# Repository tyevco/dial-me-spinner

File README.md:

# dial-me-spinner

**Docs site:** <https://tyevco.github.io/dial-me-spinner/>

A Bluetooth dial spinner about 70 mm across, built on the nRF52840. A heavy,
balanced stainless flywheel ring spins around a stationary centre that holds a
colour OLED and a ring of 48 addressable RGB LEDs. You can press the whole top
to click. A tiny actuator switches the ring electronically between **free
spin** and **magnetic click detents**, and it holds either position with zero
power.

The same hardware serves three uses:

* **Game / decision spinner.** You flick the ring and a prize wheel animates on
  the LEDs and the OLED, with a tick on every detent and the result shown when
  it stops.
* **PC / phone controller.** It works like a Surface Dial: a BLE or USB HID
  Radial Controller on Windows, and a wheel or consumer-control device on
  macOS, Linux, Android and iOS.
* **Fidget toy.** Long free spins or clicky spins, with a spin and RPM counter.

> **Status: rev A. Schematics and both PCBs are generated and routed, and the
> fab outputs are written; nothing has been built or tested.** The schematics
> of both boards pass ERC. The only report is one intended pin pair that
> `build.py` waives and lists (U21's QOD tied to its VOUT). Both boards are
> placed and routed by `layout.py` (Freerouting first, then the grid router
> `finish_route.py` for the connections it leaves open) and pass KiCad DRC with
> schematic parity: 0 errors and 0 unconnected on both, no warnings on the main
> board, two silk-to-edge warnings on the base board. `release.py` wrote the
> fab outputs into `hardware/fab/main/` and `hardware/fab/base/` only after
> that gate passed. The mechanical model's clash check of the routed boards
> reports only the intended contacts. A SPICE suite (`hardware/sim/`, [docs/simulation.md](docs/simulation.md))
> checks the analog design against the netlists; the part changes it drove
> are in the schematics. No prototype has been built and no firmware has been written.
> Every runtime, force and spin-time figure in the docs is a calculation or
> simulation that still has to be verified on a prototype.

## Features (rev A design)

| | |
|---|---|
| Size | Ø70 × 36 mm. Stationary centre, spinning 316L stainless ring (≈ 117 g, OD 70 / ID 54 / 10 mm) on a single 608 bearing |
| Detents | 24 clicks per turn, strength continuously variable from 0 to about 16.5 mN·m, or free spin (the detent magnet's residual cogging is 2.7 µN·m; the stepper's own cogging still has to be bench-tested, [mechanical §7](docs/mechanical.md#7-detent-mechanism)). Switched by a micro linear stepper with a self-locking lead screw (zero holding power) |
| Rotation sensing | TI TMAG5273 3D Hall sensor reading the same 48-magnet track. Interpolated angle, about 0.05–0.1° after self-calibration, plus µA-level wake on rotation |
| Display | 1.5 in 128×128 RGB PMOLED (SSD1351) behind a Ø30 mm round window |
| Lights | 48 × WS2812C-2020-V6 RGB LEDs under an opal diffuser ring, 2 per detent |
| Input | Press-down click (the whole top floats on springs over a centre switch), rotation, tap and pick-up (LIS2DW12 accelerometer) |
| Sound | Magnet-free piezo for detent ticks and UI beeps |
| Radio | nRF52840 module (Raytac MDBT50Q-U1MV2, u.FL) with an off-board flex antenna in the base. BLE HID, a custom GATT service for a companion app, and USB HID |
| NFC | NFC-A tag emulation (Type 2 / Type 4) on the nRF52840 NFCT, with a coil in the top cover. Phones read it; the spinner cannot read tags (the phone app reads one and sends the content over BLE) |
| Power | 1S LiPo of about 1000 mAh, TI BQ25180 power-path charger, USB-C. Ship mode, about 38 µA sleep (25 °C typical; [power budget](docs/architecture.md#8-power-budget-and-battery-life)) |
| Estimated runtime | About 9 h of continuous game mode, about 4 weeks of typical desk-controller use per charge (see the [power budget](docs/architecture.md#8-power-budget-and-battery-life)) |

## Documentation

| Document | Contents |
|---|---|
| [docs/architecture.md](docs/architecture.md) | System overview, how each requirement is met, block diagram, board partition and link, subsystem decisions with the alternatives that were rejected, power tree, power budget and battery life, RF strategy, risk register, open decisions, rough BOM cost |
| [docs/assembly.md](docs/assembly.md) | Fabrication and assembly: JLCPCB order settings, sourcing, the link harness and antenna coax, magnet track, bearing prep, rotor balancing, mechanical assembly order |
| [docs/bringup.md](docs/bringup.md) | Bring-up and acceptance tests (steps B-x), from bare PCBA to an accepted unit |
| [docs/mechanical.md](docs/mechanical.md) | Mechanical design: stack-up and where SPEC §8 is not buildable as written, bearing, flywheel and balancing, magnet track, detent mechanism, press click, antenna placement, drop, feet, assembly order, mechanical BOM, calculations |
| [docs/firmware.md](docs/firmware.md) | Firmware architecture plan (nRF Connect SDK / Zephyr, MCUboot), including the BQ25180 register init table (§13.1). A plan only: no firmware code exists yet |
| [docs/simulation.md](docs/simulation.md) | The SPICE suite in `hardware/sim/`: how to run it, how a test is built, what each block covers; the latest values are on its [results page](hardware/sim/results/report.md) |
| [docs/display-study.md](docs/display-study.md) | Rev-B study (future work): a larger round touch AMOLED. Rev A keeps the SSD1351 OLED |
| [hardware/design/SPEC.md](hardware/design/SPEC.md) | **Architecture of record** for the schematics: boards, link pinout, power tree, nRF52840 pin map, per-sheet contents, mechanical stack-up |
| [hardware/tools/README.md](hardware/tools/README.md) | The Python → KiCad generator toolchain |

## Repository layout

```
docs/                    design documentation (start with architecture.md;
                         simulation.md for the SPICE suite, display-study.md
                         for rev B)
hardware/
  design/                the circuit as code
    SPEC.md              architecture of record (what the schematics implement)
    nets.py              pin map and the shared net names (the "capture contract")
    build.py             generates the schematics (.kicad_sch), project file and
                         netlist from the sheet modules, and runs ERC
    layout.py            generates the boards (.kicad_pcb) from the netlists:
                         SPEC §8 placement of the constrained parts, clustering
                         of the rest, outline, keep-outs, zones, fiducials,
                         optional Freerouting autoroute, then the grid router
                         (hardware/tools/finish_route.py) for what it leaves
                         open, clean-up (GND stitching vias, silkscreen
                         references), then DRC
    release.py           fab and review outputs into hardware/fab/<board>/:
                         gerbers, JLCPCB BOM + CPL, ORDER-NOTES.md, schematic and
                         board PDFs, 3D renders; refuses to write them unless DRC
                         and schematic parity are clean
    jlc_offsets.json     cached per-LCSC-part rotation/origin corrections for the
                         JLC CPL (written by tools/jlc_cpl.py)
    sheets/              one Python module per schematic sheet
                         main board: main_power, mcu, display, leds, sensors, detent
                         base board: base
  tools/                 generator toolchain: S-expression I/O, symbol/footprint
                         generation, schematic writer, PCB builder, placer, fab outputs
    finish_route.py      grid router that completes the connections Freerouting
                         leaves open (A* on F.Cu / In2.Cu / B.Cu with through
                         vias, rip-up of unlocked signal copper); KiCad DRC
                         re-checks every connection it adds
    silk.py              places silkscreen references clear of pads, other silk
                         and the board edge
    jlc_cpl.py           fits JLC's EasyEDA footprints to the KiCad ones and writes
                         the CPL (top θ+α, bottom 180−θ+α); simulates JLC's
                         placement of every row and stops on a pad off copper
    tests/               CPL check tests (pytest; needs pcbnew)
  kicad/                 generated KiCad 10 projects (main/, base/): schematics from
                         build.py, .kicad_pcb from layout.py
  fab/                   generated by release.py, one directory per board (main/,
                         base/): gerbers.zip, *-BOM-JLCPCB.csv, *-CPL-JLCPCB.csv,
                         ORDER-NOTES.md (DNP list, bottom-side parts, board-only
                         parts), drc-parity.rpt (the DRC + schematic-parity
                         gate's report), PDFs, renders
  mechanical/            enclosure and rotor CAD (OpenSCAD), calculations, renders
                         and STLs; board parts imported from the generated PCBs
                         (extract_board_parts.py) for the clash check
  sim/                   SPICE test suite (ngspice + pytest) that builds its
                         decks from the generated netlists: tests/test_*.py,
                         IC models in models/, report written to results/
                         when run (docs/simulation.md)
firmware/                (planned) nRF Connect SDK / Zephyr application
```

The schematics in `hardware/kicad/` are **generated**. Do not hand-edit the
`.kicad_sch` files. Change the sheet modules in `hardware/design/sheets/` (and
SPEC.md or nets.py if the architecture changes), then rebuild.

## Regenerating the KiCad projects

Requirements:

* **KiCad 10** (10.0.8), providing:
  * `kicad-cli`;
  * the `pcbnew` Python module, used to write custom footprints and by
    `layout.py` and `release.py`;
  * the stock libraries and project template in `/usr/share/kicad`.
    `KICAD10_SYMBOL_DIR` overrides the symbol path (used by `build.py`).
    `KICAD10_FOOTPRINT_DIR` overrides the footprint path, and only `layout.py`
    reads it. The project template path
    (`/usr/share/kicad/template/kicad.kicad_pro`) is fixed in `schgen.py`.
* **Python 3.10+**, with numpy for `layout.py`, and matplotlib for the grid router.
* **poppler-utils** (`pdftoppm`), only for `--render`.
* Optionally `xvfb-run`, which `release.py` uses for headless 3D renders.
* For autorouting only: **Java 21** and the **Freerouting 2.1.x** jar, given
  by `FREEROUTING_JAR`.

From the repository root:

```sh
# Both boards: writes hardware/kicad/main/ and hardware/kicad/base/,
# runs ERC and exports a netlist for each
python3 hardware/design/build.py

# One board, plus a PDF and one PNG per sheet for review
python3 hardware/design/build.py --board main --render

# Scratch build of selected sheets into another directory, without ERC
python3 hardware/design/build.py --board main --only leds sensors --out /tmp/scratch --no-erc
```

Each board directory receives:
* `dial-me-spinner-<board>.kicad_pro`, the `.kicad_sch` sheets and a `.net`
  netlist;
* the ERC report `erc.rpt`;
* a project-local library in `lib/` (`dial_spinner.kicad_sym` and
  `dial_spinner.pretty`).

Open the `.kicad_pro` in KiCad 10 to inspect the result. `build.py` exits
non-zero if its own connectivity checks fail.

Boards and fab outputs (after `build.py`, which writes the netlists they read):

```sh
# Place both boards and run DRC; add --route to autoroute with Freerouting
# (--minutes N is the Freerouting time budget of the first attempt, default 30,
# and attempt k gets k x N; --attempts N, default 3, re-runs it while
# connections remain; whatever is still open then goes to the grid router;
# --resume continues routing the board as it is; --complete runs only the grid
# router on it; --finish only cleans up an already routed board)
python3 hardware/design/layout.py [--board main|base] [--route] [--minutes N] [--attempts N] [--resume] [--complete] [--finish]

# Gerbers, JLCPCB BOM + CPL, ORDER-NOTES.md, PDFs and 3D renders into
# hardware/fab/<board>/; stops if DRC or schematic parity reports an error
# (--force writes a review-only package)
python3 hardware/design/release.py [--board main|base] [--force]
```

The CPL corrections come from `hardware/design/jlc_offsets.json`, so
`release.py` needs no network access. It stops if a placed part has no entry
there; `jlc_cpl.update_offsets()` adds one by fetching that part's EasyEDA
footprint, and caches its pads. Before writing the CPL, `release.py` puts
those EasyEDA pads down at each row's point and angle, the way JLC places the
part, and stops if any pad lands off copper or on a differently numbered pad
of the same name (a symmetric package turned 180° still lands on copper, so
the numbers are the only sign). `python3 -m pytest hardware/tools/tests -q`
checks that this check passes on both boards and catches a wrong rotation or
origin. The EasyEDA footprint titles and pad centres in `jlc_offsets.json` come
from the JLCEDA/EasyEDA Official Library ([lceda.cn](https://lceda.cn/),
[easyeda.com](https://easyeda.com)), whose copyright belongs to JLCEDA/EasyEDA.

## Running the SPICE suite

The suite reads the netlists that `build.py` writes, so run it after a
schematic change. It needs ngspice 42 or newer and pytest, numpy and scipy
([docs/simulation.md](docs/simulation.md)):

```sh
python3 -m pytest hardware/sim -q                  # everything
python3 -m pytest hardware/sim -q -m "not slow"    # skip the long Monte Carlo sweeps
```

It writes `hardware/sim/results/report.md` and `results.json`. A check that
shows a real design problem is a strict `xfail` with the reason, so it cannot
quietly start passing.

## Status and next steps

* **Done:** subsystem research with independent verification. Architecture
  (SPEC.md). Generator toolchain. Schematics of both boards, ERC-clean
  apart from the one documented `build.py` waiver.
  Both boards placed and routed (`layout.py`: SPEC §8 placement of the
  constrained parts, clustering of the rest, Freerouting, then the grid router
  `finish_route.py`), DRC clean with schematic parity.
  The fab-output script `release.py`, which writes Gerbers, the JLCPCB BOM and
  CPL (rotations corrected per LCSC part), ORDER-NOTES.md, PDFs and renders
  behind a DRC and schematic-parity gate, and its outputs for both boards in
  `hardware/fab/`. The placement fixes from the
  mechanical model's clash check (module u.FL facing outward, link connector
  J1 at r 19.5, the 2.95 mm SM04B battery connector, R42 clear of the cover
  skirt), after which the check reports only the intended contacts. The SPICE
  suite in `hardware/sim/` and the part changes it drove (VBUS series resistor
  R12, a second USB ESD array U12 at the module, the OLED load switch's QOD
  tied to its output, R4 68 Ω for the LED rail discharge, 25 V VSYS caps, base
  C1 and R4). Assembly, bring-up, mechanical, simulation and firmware-plan
  documents.
* **In progress:** the SPEC items in mechanical §3A. The remaining strict
  `xfail`s of the SPICE suite are firmware-dependent rules (written into
  firmware.md and SPEC §5) or accepted rev-A risks, such as the USB ESD
  margin with a short harness, the actuator thrust and the OLED boost's
  FB-bias spread ([docs/simulation.md](docs/simulation.md)).
* **Not done:** no prototype has been built or tested, and no firmware code has
  been written. Every item marked "to verify on prototype" in the docs is
  still open. The detent actuator's thrust margin is open (architecture risk
  R4).
* **Next:**
  * close the pre-order checks in [assembly §2.4](docs/assembly.md#24-pre-order-checks-do-them-in-the-gerber-viewer-not-only-in-kicad)
    and [§13](docs/assembly.md#13-open-items-and-tvp-list-assembly)
    (LED-cavity silk, boost-inductor spacing), then order both boards with
    the outputs in `hardware/fab/main/` and `hardware/fab/base/`: two-sided assembly
    for the main board, top side only for the base board (4-layer, ENIG), the
    MDBT50Q through JLC Global Sourcing or consignment, the DNP list from
    ORDER-NOTES.md;
  * a printed mechanical mock-up to check the antenna shelf, the harness and
    coax path and the ring's ESD bleed path, and to measure the RF antenna
    (VNA/RSSI), spin-down and detent feel, plus a bench test of the stepper's
    free-mode cogging before the PCB order;
  * bring-up of the first prototype ([docs/bringup.md](docs/bringup.md)) and
    the items to verify on it;
  * firmware, following [docs/firmware.md](docs/firmware.md).
* Known issues and open decisions are tracked in
  [architecture §10–§13](docs/architecture.md#10-risk-register) and
  [assembly §13](docs/assembly.md#13-open-items-and-tvp-list-assembly).

Long-lead parts to order early: the SSD1351 OLED panel (0 stock at major
distributors in Oct 2026), the MDBT50Q-U1MV2 module (0 stock at JLC: use JLC
Global Sourcing or consign it) and the Molex 146153-0100 antenna (DigiKey/Mouser;
LCSC stocks only the -0050, which is too short).

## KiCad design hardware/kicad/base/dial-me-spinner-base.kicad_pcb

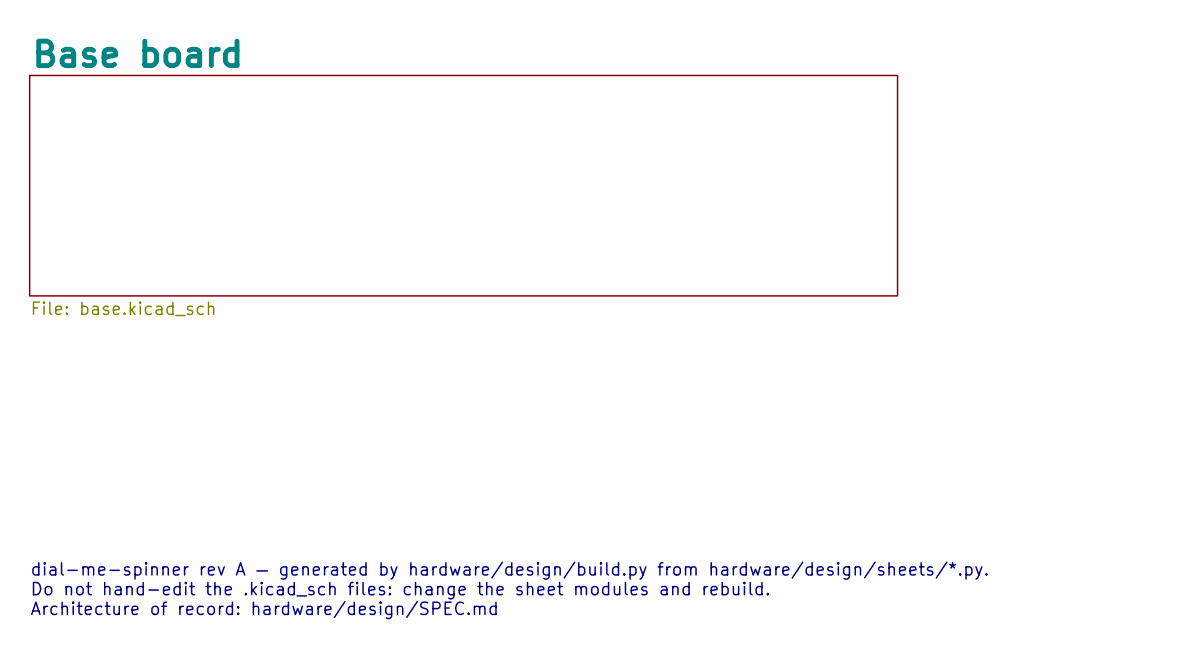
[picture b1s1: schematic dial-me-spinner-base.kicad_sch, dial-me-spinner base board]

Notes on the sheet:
dial-me-spinner rev A — generated by hardware/design/build.py from hardware/design/sheets/*.py. Do not hand-edit the .kicad_sch files: change the sheet modules and rebuild. Architecture of record: hardware/design/SPEC.md

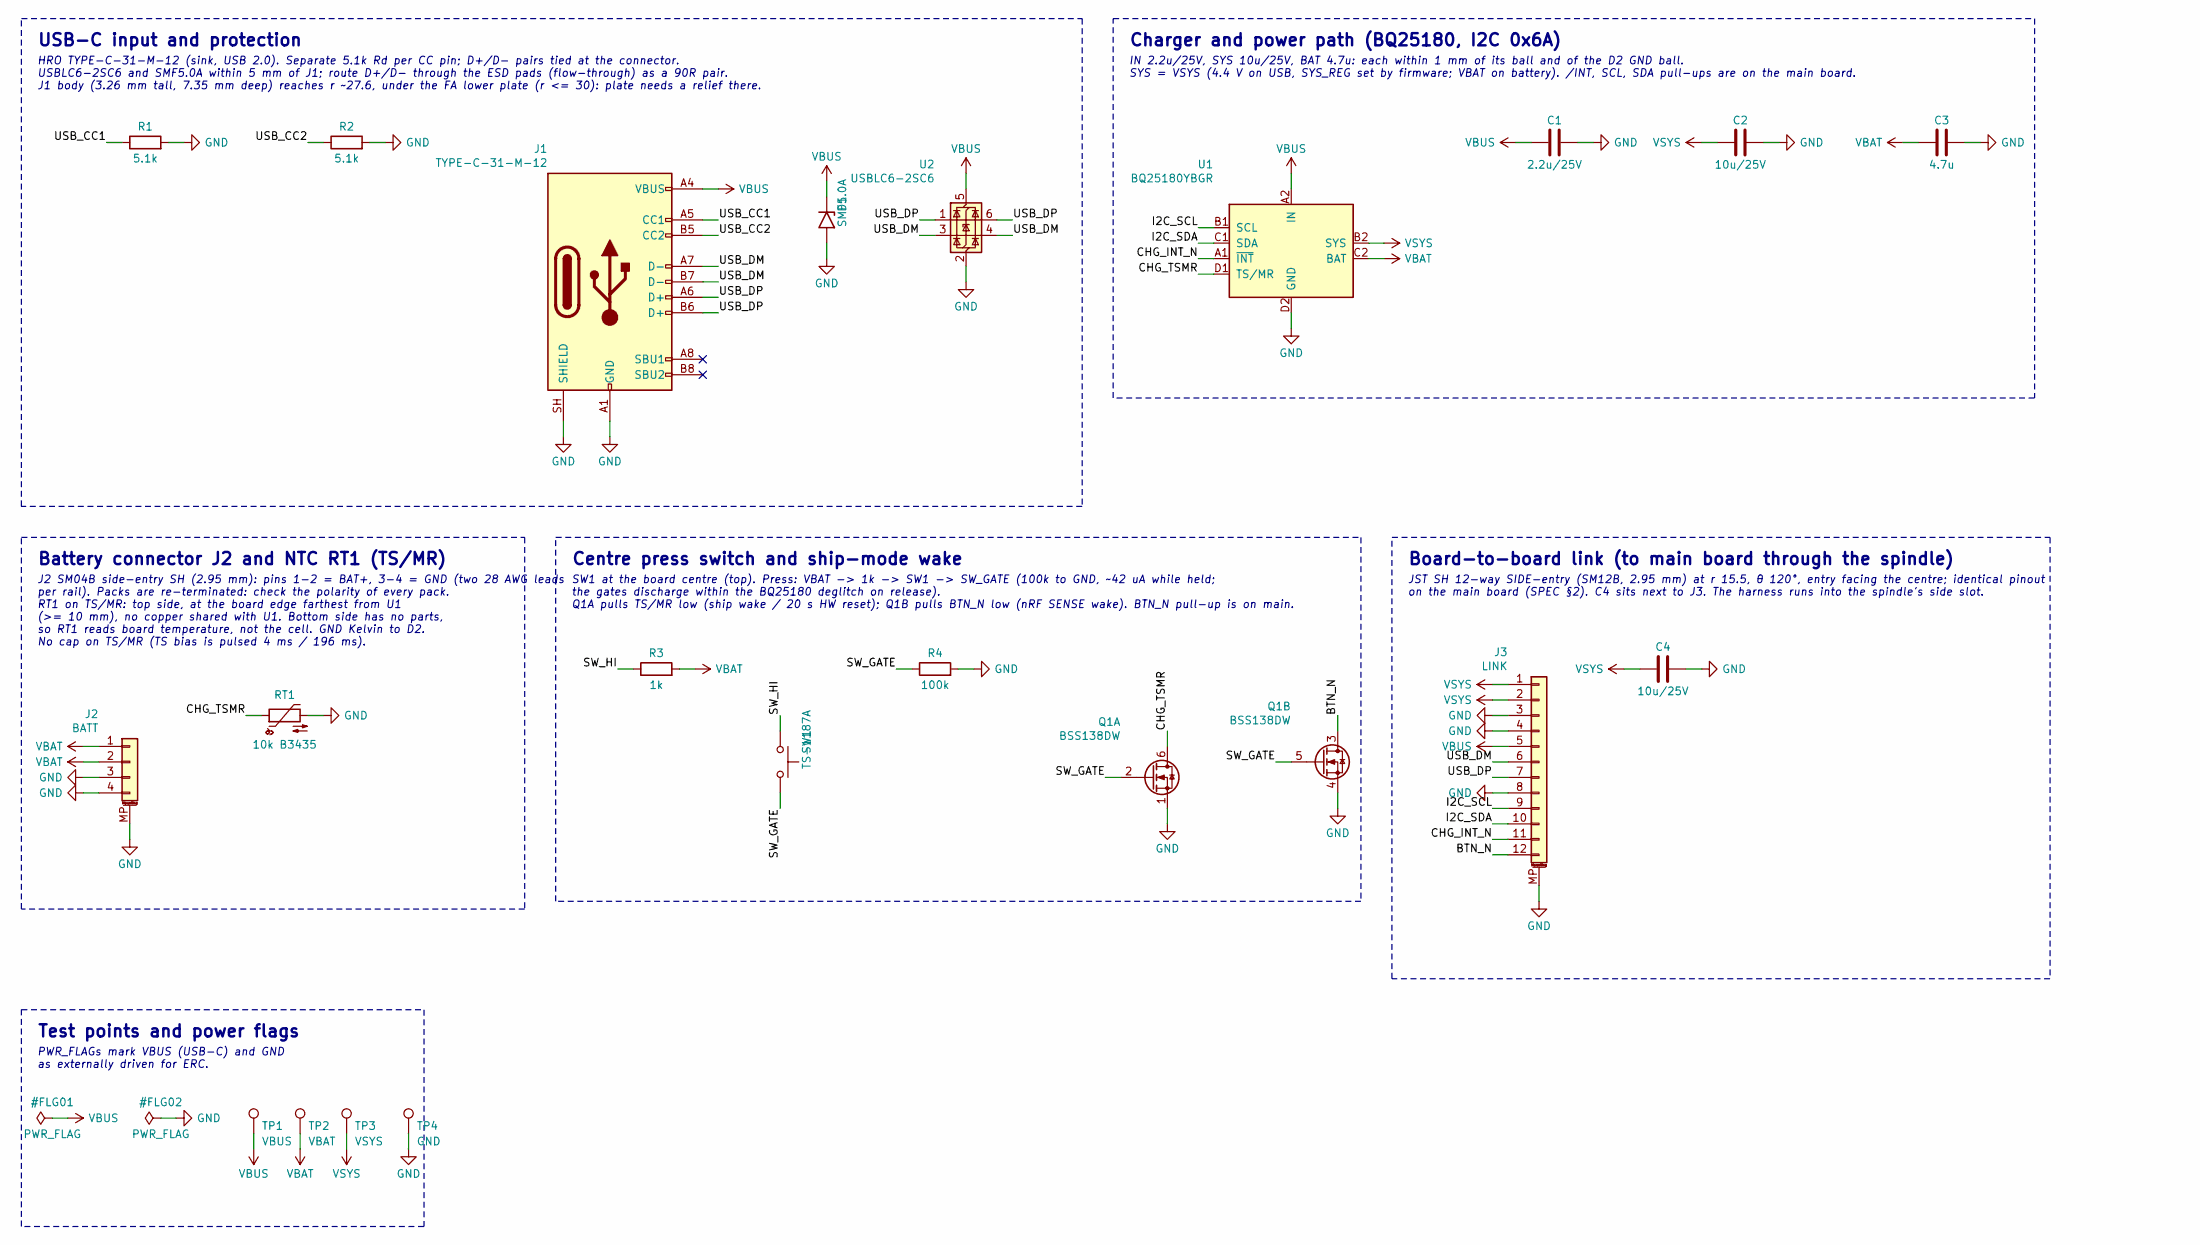
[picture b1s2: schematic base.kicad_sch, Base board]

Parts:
C1: 2.2u/25V; C_0805_2012Metric; MPN CC0805KKX7R8BB225; LCSC C277470
C2, C4: 10u/25V; C_0603_1608Metric; MPN CL10A106MA8NRNC; LCSC C96446
C3: 4.7u; C_0603_1608Metric; MPN CL10A475KO8NNNC; LCSC C19666
D1: SMF5.0A; D_SMF; MPN SMF5.0A; LCSC C151296
J1: TYPE-C-31-M-12; USB_C_Receptacle_HRO_TYPE-C-31-M-12; MPN TYPE-C-31-M-12; LCSC C165948
J2: BATT; JST_SH_SM04B-SRSS-TB_1x04-1MP_P1.00mm_Horizontal; MPN SM04B-SRSS-TB(LF)(SN); LCSC C160404
J3: LINK; JST_SH_SM12B-SRSS-TB_1x12-1MP_P1.00mm_Horizontal; MPN SM12B-SRSS-TB(LF)(SN); LCSC C160411
Q1: BSS138DW; SOT-363_SC-70-6; MPN BSS138DW-7-F; LCSC C154900
R1, R2: 5.1k; R_0402_1005Metric; MPN 0402WGF5101TCE; LCSC C25905
R3: 1k; R_0402_1005Metric; MPN 0402WGF1001TCE; LCSC C11702
R4: 100k; R_0402_1005Metric; MPN 0402WGF1003TCE; LCSC C25741
RT1: 10k B3435; R_0402_1005Metric; MPN NCP15XH103F03RC; LCSC C77131
SW1: TS-1187A; SW_Push_1P1T_XKB_TS-1187A; MPN TS-1187A-B-A-B; LCSC C318884
TP1: VBUS; TestPoint_Pad_D1.0mm
TP2: VBAT; TestPoint_Pad_D1.0mm
TP3: VSYS; TestPoint_Pad_D1.0mm
TP4: GND; TestPoint_Pad_D1.0mm
U1: BQ25180YBGR; Texas_DSBGA-8_1.04x1.59mm_Layout2x4_P0.4mm_YBG0008; MPN BQ25180YBGR; LCSC C3682423
U2: USBLC6-2SC6; SOT-23-6; MPN USBLC6-2SC6; LCSC C7519

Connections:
/Base board/BTN_N: J3.12, Q1.3 (D)
/Base board/CHG_INT_N: J3.11, U1.A1 (~INT)
/Base board/CHG_TSMR: Q1.6 (D), RT1.1, U1.D1 (TS/MR)
/Base board/I2C_SCL: J3.9, U1.B1 (SCL)
/Base board/I2C_SDA: J3.10, U1.C1 (SDA)
/Base board/SW_GATE: Q1.2 (G), Q1.5 (G), R4.1, SW1.2
/Base board/SW_HI: R3.1, SW1.1
/Base board/USB_CC1: J1.A5 (CC1), R1.1
/Base board/USB_CC2: J1.B5 (CC2), R2.1
/Base board/USB_DM: J1.A7 (D-), J1.B7 (D-), J3.6, U2.3 (I/O2), U2.4 (I/O2)
/Base board/USB_DP: J1.A6 (D+), J1.B6 (D+), J3.7, U2.1 (I/O1), U2.6 (I/O1)
GND: C1.2, C2.2, C3.2, C4.2, D1.2 (A2), J1.A1 (GND), J1.A12 (GND), J1.B1 (GND), J1.B12 (GND), J1.SH (SHIELD), J2.3, J2.4, J2.MP (MountPin), J3.3, J3.4, J3.8, J3.MP (MountPin), Q1.1 (S), Q1.4 (S), R1.2, R2.2, R4.2, RT1.2, TP4.1, U1.D2 (GND), U2.2 (GND)
VBAT: C3.1, J2.1, J2.2, R3.2, TP2.1, U1.C2 (BAT)
VBUS: C1.1, D1.1 (A1), J1.A4 (VBUS), J1.A9 (VBUS), J1.B4 (VBUS), J1.B9 (VBUS), J3.5, TP1.1, U1.A2 (IN), U2.5 (VBUS)
VSYS: C2.1, C4.1, J3.1, J3.2, TP3.1, U1.B2 (SYS)

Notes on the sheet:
USB-C input and protection
HRO TYPE-C-31-M-12 (sink, USB 2.0). Separate 5.1k Rd per CC pin; D+/D- pairs tied at the connector. USBLC6-2SC6 and SMF5.0A within 5 mm of J1; route D+/D- through the ESD pads (flow-through) as a 90R pair. J1 body (3.26 mm tall, 7.35 mm deep) reaches r ~27.6, under the FA lower plate (r <= 30): pla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
Charger and power path (BQ25180, I2C 0x6A)
IN 2.2u/25V, SYS 10u/25V, BAT 4.7u: each within 1 mm of its ball and of the D2 GND ball. SYS = VSYS (4.4 V on USB, SYS_REG set by firmware; VBAT on battery). /INT, SCL, SDA pull-ups are on the main board.
Battery connector J2 and NTC RT1 (TS/MR)
J2 SM04B side-entry SH (2.95 mm): pins 1-2 = BAT+, 3-4 = GND (two 28 AWG leads per rail). Packs are re-terminated: check the polarity of every pack. RT1 on TS/MR: top side, at the board edge farthest from U1 (>= 10 mm), no copper shared with U1. Bottom side has no parts, so RT1 reads board temperat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
Centre press switch and ship-mode wake
SW1 at the board centre (top). Press: VBAT -> 1k -> SW1 -> SW_GATE (100k to GND, ~42 uA while held; the gates discharge within the BQ25180 deglitch on release). Q1A pulls TS/MR low (ship wake / 20 s HW reset); Q1B pulls BTN_N low (nRF SENSE wake). BTN_N pull-up is on main.
Board-to-board link (to main board through the spindle)
JST SH 12-way SIDE-entry (SM12B, 2.95 mm) at r 15.5, θ 120°, entry facing the centre; identical pinout on the main board (SPEC §2). C4 sits next to J3. The harness runs into the spindle's side slot.
Test points and power flags
PWR_FLAGs mark VBUS (USB-C) and GND as externally driven for ERC.

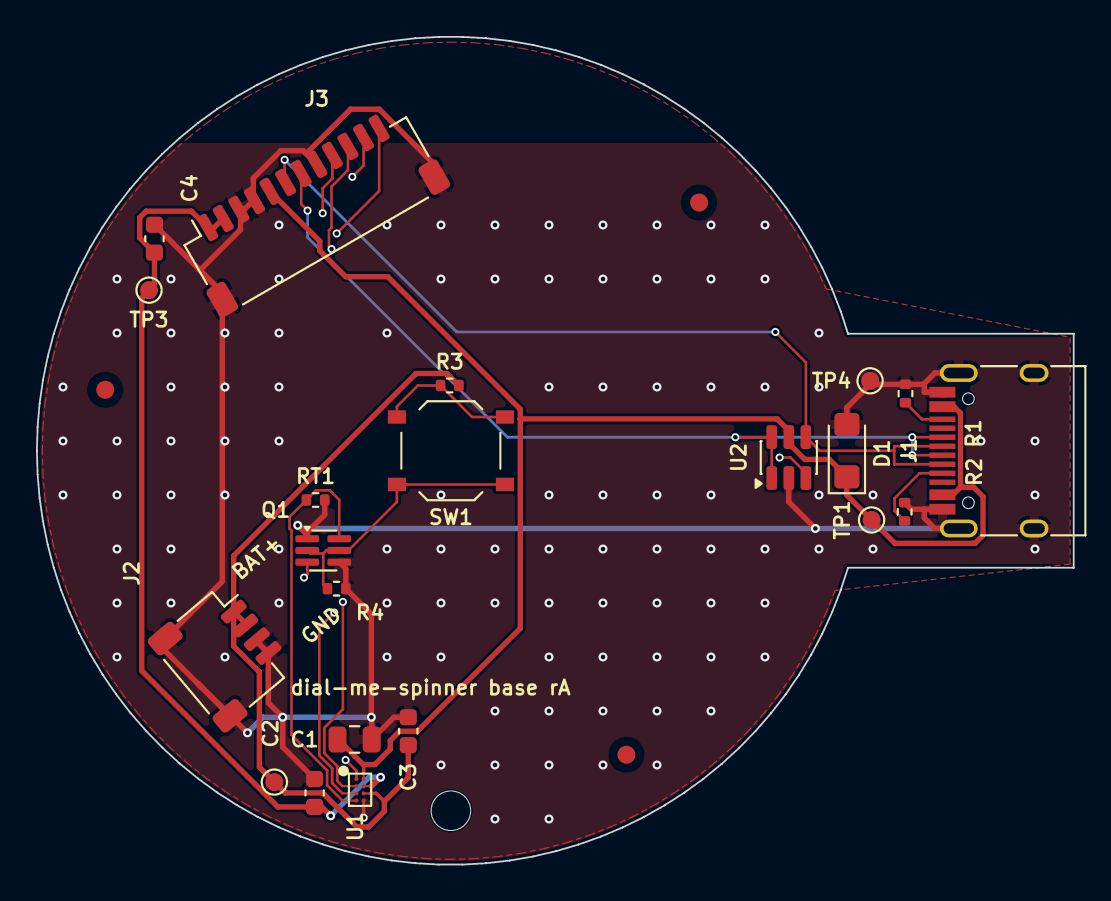
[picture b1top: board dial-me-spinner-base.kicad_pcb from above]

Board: 4 copper layers, 57.6 x 46.0 mm, 25 parts (0 on the bottom side), 15 nets.

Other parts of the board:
FID1, FID2, FID3: Fiducial_1mm_Mask2mm
H1: MountingHole_2.2mm_M2

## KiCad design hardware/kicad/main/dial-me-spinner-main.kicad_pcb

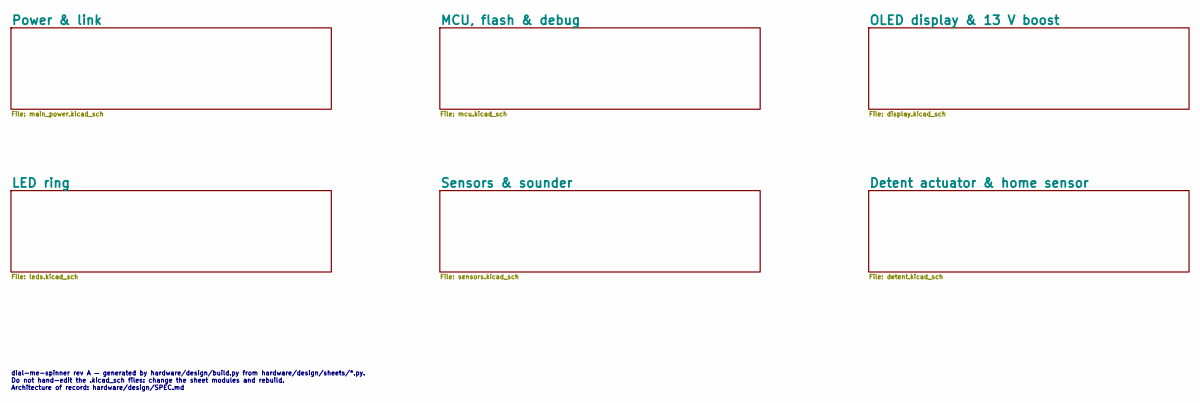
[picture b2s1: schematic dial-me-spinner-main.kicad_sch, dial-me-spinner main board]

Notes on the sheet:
dial-me-spinner rev A — generated by hardware/design/build.py from hardware/design/sheets/*.py. Do not hand-edit the .kicad_sch files: change the sheet modules and rebuild. Architecture of record: hardware/design/SPEC.md

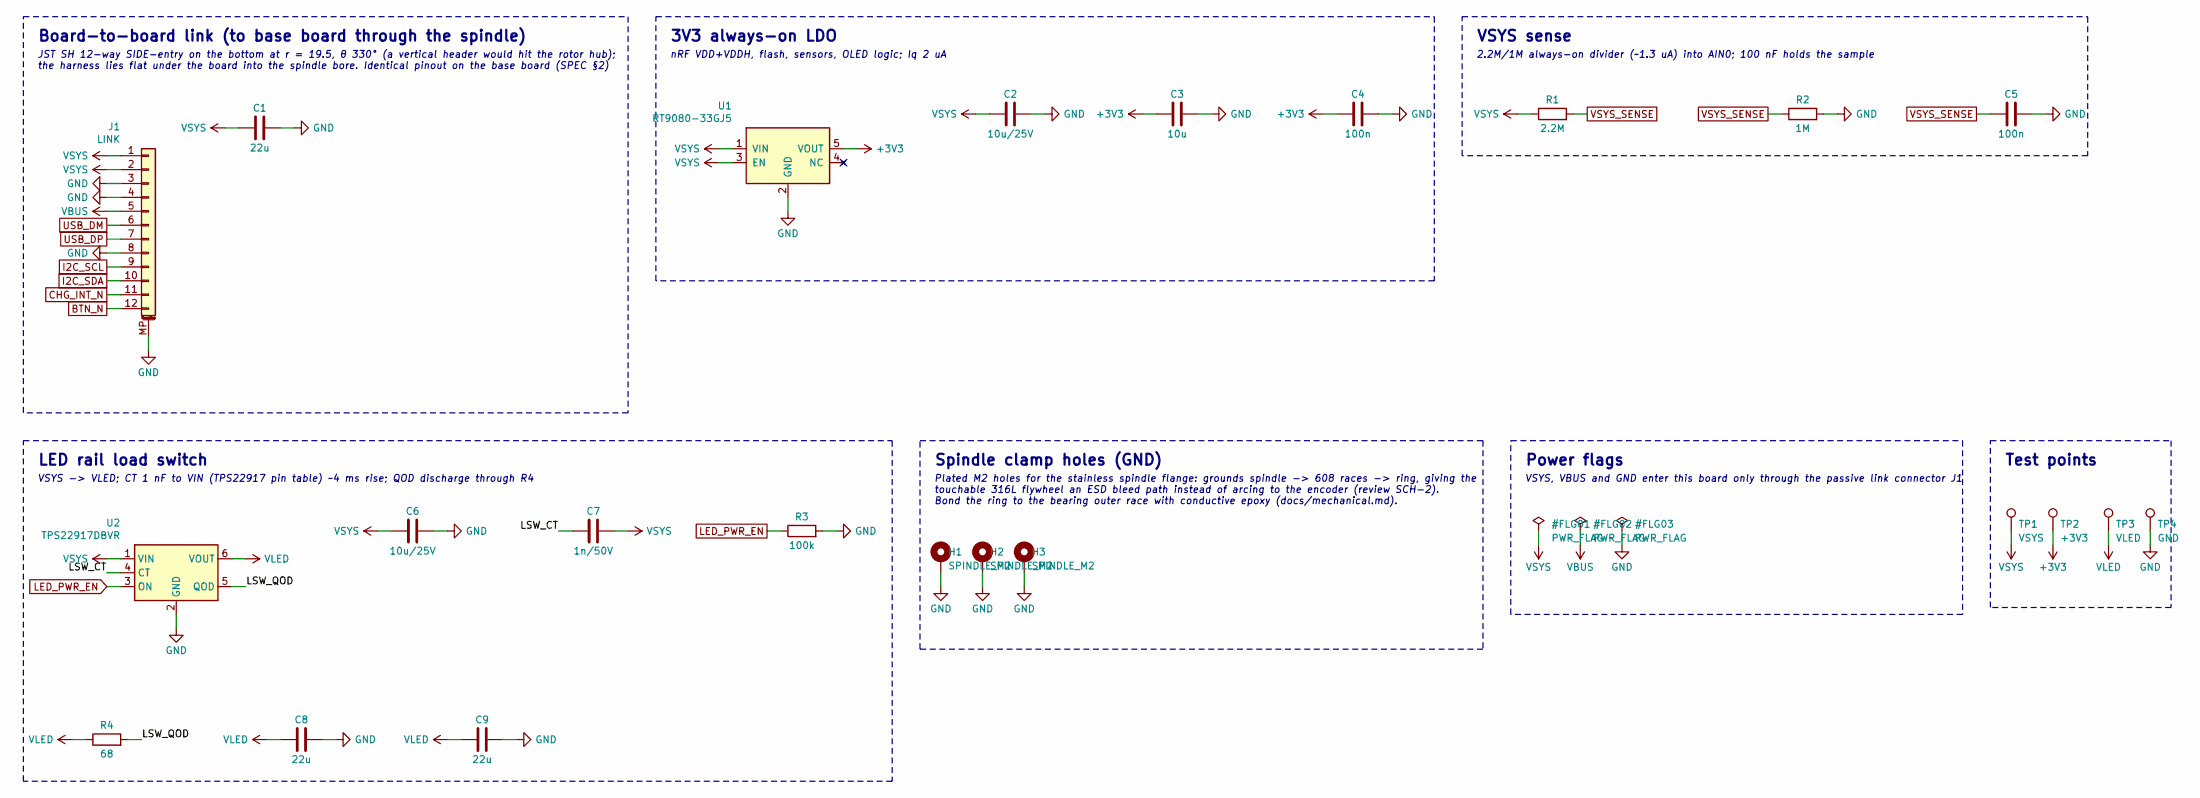
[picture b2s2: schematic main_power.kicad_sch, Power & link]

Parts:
C1, C8, C9: 22u; C_0805_2012Metric; MPN CL21A226MAQNNNE; LCSC C45783
C2, C6: 10u/25V; C_0603_1608Metric; MPN CL10A106MA8NRNC; LCSC C96446
C3: 10u; C_0603_1608Metric; MPN CL10A106KP8NNNC; LCSC C19702
C4, C5: 100n; C_0402_1005Metric; MPN CL05B104KO5NNNC; LCSC C1525
C7: 1n/50V; C_0402_1005Metric; MPN 0402B102K500NT; LCSC C1523
H1, H2, H3: SPINDLE_M2; MountingHole_2.2mm_M2_Pad_Via
J1: LINK; JST_SH_SM12B-SRSS-TB_1x12-1MP_P1.00mm_Horizontal; MPN SM12B-SRSS-TB(LF)(SN); LCSC C160411
R1: 2.2M; R_0402_1005Metric; MPN 0402WGF2204TCE; LCSC C11490
R2: 1M; R_0402_1005Metric; MPN 0402WGF1004TCE; LCSC C26083
R3: 100k; R_0402_1005Metric; MPN 0402WGF1003TCE; LCSC C25741
R4: 68; R_0402_1005Metric; MPN RC0402FR-0768RL; LCSC C163455
TP1: VSYS; TestPoint_Pad_D1.0mm
TP2: +3V3; TestPoint_Pad_D1.0mm
TP3: VLED; TestPoint_Pad_D1.0mm
TP4: GND; TestPoint_Pad_D1.0mm
U1: RT9080-33GJ5; SOT-23-5; MPN RT9080-33GJ5; LCSC C841192
U2: TPS22917DBVR; SOT-23-6; MPN TPS22917DBVR; LCSC C2681320

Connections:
+3V3: C3.1, C4.1, TP2.1, U1.5 (VOUT); also elsewhere on the board
/Power & link/LSW_CT: C7.1, U2.4 (CT)
/Power & link/LSW_QOD: R4.2, U2.5 (QOD)
BTN_N: J1.12; also elsewhere on the board
CHG_INT_N: J1.11; also elsewhere on the board
GND: C1.2, C2.2, C3.2, C4.2, C5.2, C6.2, C8.2, C9.2, H1.1, H2.1, H3.1, J1.3, J1.4, J1.8, J1.MP (MountPin), R2.2, R3.2, TP4.1, U1.2 (GND), U2.2 (GND); also elsewhere on the board
I2C_SCL: J1.9; also elsewhere on the board
I2C_SDA: J1.10; also elsewhere on the board
LED_PWR_EN: R3.1, U2.3 (ON); also elsewhere on the board
USB_DM: J1.6; also elsewhere on the board
USB_DP: J1.7; also elsewhere on the board
VBUS: J1.5; also elsewhere on the board
VLED: C8.1, C9.1, R4.1, TP3.1, U2.6 (VOUT); also elsewhere on the board
VSYS: C1.1, C2.1, C6.1, C7.2, J1.1, J1.2, R1.1, TP1.1, U1.1 (VIN), U1.3 (EN), U2.1 (VIN); also elsewhere on the board
VSYS_SENSE: C5.1, R1.2, R2.1; also elsewhere on the board

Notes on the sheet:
Board-to-board link (to base board through the spindle)
JST SH 12-way SIDE-entry on the bottom at r = 19.5, θ 330° (a vertical header would hit the rotor hub); the harness lies flat under the board into the spindle bore. Identical pinout on the base board (SPEC §2)
3V3 always-on LDO
nRF VDD+VDDH, flash, sensors, OLED logic; Iq 2 uA
VSYS sense
2.2M/1M always-on divider (~1.3 uA) into AIN0; 100 nF holds the sample
LED rail load switch
VSYS -> VLED; CT 1 nF to VIN (TPS22917 pin table) ~4 ms rise; QOD discharge through R4
Spindle clamp holes (GND)
Plated M2 holes for the stainless spindle flange: grounds spindle -> 608 races -> ring, giving the touchable 316L flywheel an ESD bleed path instead of arcing to the encoder (review SCH-2). Bond the ring to the bearing outer race with conductive epoxy (docs/mechanical.md).
Power flags
VSYS, VBUS and GND enter this board only through the passive link connector J1
Test points

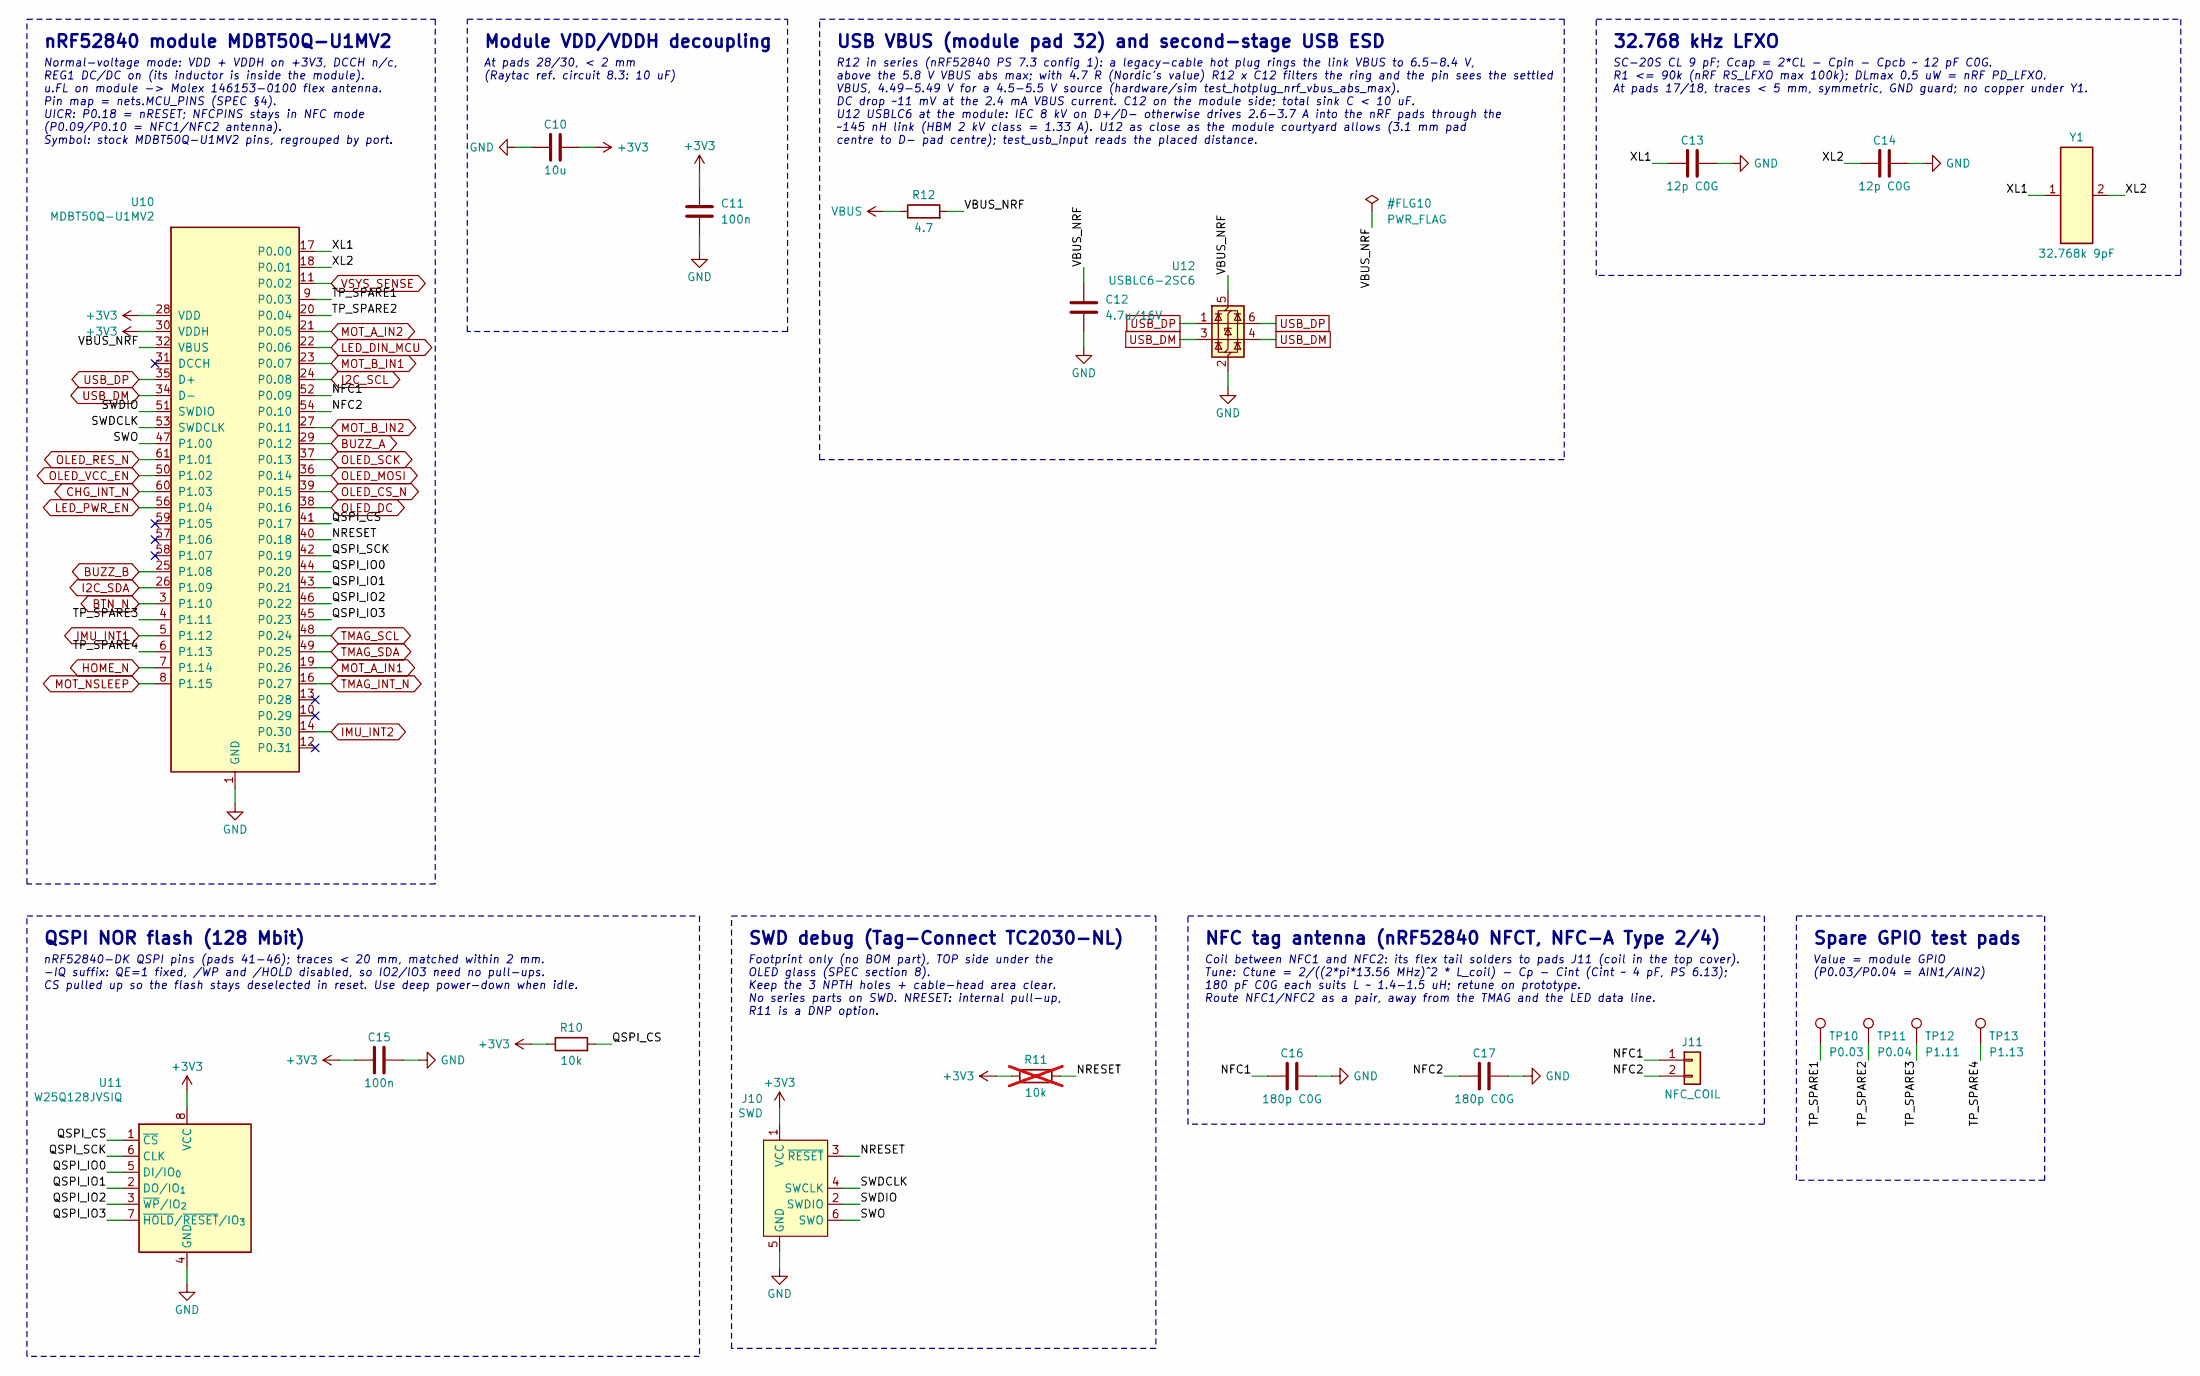
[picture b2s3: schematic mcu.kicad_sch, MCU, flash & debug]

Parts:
C10: 10u; C_0603_1608Metric; MPN CL10A106KP8NNNC; LCSC C19702
C11, C15: 100n; C_0402_1005Metric; MPN CL05B104KO5NNNC; LCSC C1525
C12: 4.7u/16V; C_0603_1608Metric; MPN CL10A475KO8NNNC; LCSC C19666
C13, C14: 12p C0G; C_0402_1005Metric; MPN 0402CG120J500NT; LCSC C1547
C16, C17: 180p C0G; C_0402_1005Metric; MPN 0402CG181J500NT; LCSC C78636
J10: SWD; Tag-Connect_TC2030-IDC-NL_2x03_P1.27mm_Vertical; MPN TC2030-IDC-NL (footprint only)
J11: NFC_COIL; NFC_Coil_Pads_1x02_P2.0mm
R10: 10k; R_0402_1005Metric; MPN 0402WGF1002TCE; LCSC C25744
R11: 10k; R_0402_1005Metric; MPN 0402WGF1002TCE; LCSC C25744; not fitted
R12: 4.7; R_0402_1005Metric; MPN FRC0402F4R70TS; LCSC C2909356
TP10: P0.03; TestPoint_Pad_D1.0mm
TP11: P0.04; TestPoint_Pad_D1.0mm
TP12: P1.11; TestPoint_Pad_D1.0mm
TP13: P1.13; TestPoint_Pad_D1.0mm
U10: MDBT50Q-U1MV2; Raytac_MDBT50Q_UFL; MPN MDBT50Q-U1MV2; LCSC C2688382
U11: W25Q128JVSIQ; SOIC-8_5.3x5.3mm_P1.27mm; MPN W25Q128JVSIQ; LCSC C97521
U12: USBLC6-2SC6; SOT-23-6; MPN USBLC6-2SC6; LCSC C7519
Y1: 32.768k 9pF; Crystal_SII_SC-20S_2.0x1.2mm; MPN SC-20S 32.768kHz 20PPM 9pF; LCSC C97603

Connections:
+3V3: C10.1, C11.1, C15.1, J10.1 (VCC), R10.1, R11.1, U10.28 (VDD), U10.30 (VDDH), U11.8 (VCC); also elsewhere on the board
/MCU, flash & debug/NFC1: C16.1, J11.1, U10.52 (P0.09)
/MCU, flash & debug/NFC2: C17.1, J11.2, U10.54 (P0.10)
/MCU, flash & debug/NRESET: J10.3 (~RESET), R11.2, U10.40 (P0.18)
/MCU, flash & debug/QSPI_CS: R10.2, U10.41 (P0.17), U11.1 (~CS)
/MCU, flash & debug/QSPI_IO0: U10.44 (P0.20), U11.5 (DI/IO_{0})
/MCU, flash & debug/QSPI_IO1: U10.43 (P0.21), U11.2 (DO/IO_{1})
/MCU, flash & debug/QSPI_IO2: U10.46 (P0.22), U11.3 (~WP/IO_{2})
/MCU, flash & debug/QSPI_IO3: U10.45 (P0.23), U11.7 (~HOLD/~RESET/IO_{3})
/MCU, flash & debug/QSPI_SCK: U10.42 (P0.19), U11.6 (CLK)
/MCU, flash & debug/SWDCLK: J10.4 (SWCLK), U10.53 (SWDCLK)
/MCU, flash & debug/SWDIO: J10.2 (SWDIO), U10.51 (SWDIO)
/MCU, flash & debug/SWO: J10.6 (SWO), U10.47 (P1.00)
/MCU, flash & debug/TP_SPARE1: TP10.1, U10.9 (P0.03)
/MCU, flash & debug/TP_SPARE2: TP11.1, U10.20 (P0.04)
/MCU, flash & debug/TP_SPARE3: TP12.1, U10.4 (P1.11)
/MCU, flash & debug/TP_SPARE4: TP13.1, U10.6 (P1.13)
/MCU, flash & debug/VBUS_NRF: C12.1, R12.2, U10.32 (VBUS), U12.5 (VBUS)
/MCU, flash & debug/XL1: C13.1, U10.17 (P0.00), Y1.1
/MCU, flash & debug/XL2: C14.1, U10.18 (P0.01), Y1.2
BTN_N: U10.3 (P1.10); also elsewhere on the board
BUZZ_A: U10.29 (P0.12); also elsewhere on the board
BUZZ_B: U10.25 (P1.08); also elsewhere on the board
CHG_INT_N: U10.60 (P1.03); also elsewhere on the board
GND: C10.2, C11.2, C12.2, C13.2, C14.2, C15.2, C16.2, C17.2, J10.5 (GND), U10.1 (GND), U10.2 (GND), U10.15 (GND), U10.33 (GND), U10.55 (GND), U11.4 (GND), U12.2 (GND); also elsewhere on the board
HOME_N: U10.7 (P1.14); also elsewhere on the board
I2C_SCL: U10.24 (P0.08); also elsewhere on the board
I2C_SDA: U10.26 (P1.09); also elsewhere on the board
IMU_INT1: U10.5 (P1.12); also elsewhere on the board
IMU_INT2: U10.14 (P0.30); also elsewhere on the board
LED_DIN_MCU: U10.22 (P0.06); also elsewhere on the board
LED_PWR_EN: U10.56 (P1.04); also elsewhere on the board
MOT_A_IN1: U10.19 (P0.26); also elsewhere on the board
MOT_A_IN2: U10.21 (P0.05); also elsewhere on the board
MOT_B_IN1: U10.23 (P0.07); also elsewhere on the board
MOT_B_IN2: U10.27 (P0.11); also elsewhere on the board
MOT_NSLEEP: U10.8 (P1.15); also elsewhere on the board
OLED_CS_N: U10.39 (P0.15); also elsewhere on the board
OLED_DC: U10.38 (P0.16); also elsewhere on the board
OLED_MOSI: U10.36 (P0.14); also elsewhere on the board
OLED_RES_N: U10.61 (P1.01); also elsewhere on the board
OLED_SCK: U10.37 (P0.13); also elsewhere on the board
OLED_VCC_EN: U10.50 (P1.02); also elsewhere on the board
TMAG_INT_N: U10.16 (P0.27); also elsewhere on the board
TMAG_SCL: U10.48 (P0.24); also elsewhere on the board
TMAG_SDA: U10.49 (P0.25); also elsewhere on the board
USB_DM: U10.34 (D-), U12.3 (I/O2), U12.4 (I/O2); also elsewhere on the board
USB_DP: U10.35 (D+), U12.1 (I/O1), U12.6 (I/O1); also elsewhere on the board
VBUS: R12.1; also elsewhere on the board
VSYS_SENSE: U10.11 (P0.02); also elsewhere on the board

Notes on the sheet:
nRF52840 module MDBT50Q-U1MV2
Normal-voltage mode: VDD + VDDH on +3V3, DCCH n/c, REG1 DC/DC on (its inductor is inside the module). u.FL on module -> Molex 146153-0100 flex antenna. Pin map = nets.MCU_PINS (SPEC §4). UICR: P0.18 = nRESET; NFCPINS stays in NFC mode (P0.09/P0.10 = NFC1/NFC2 antenna). Symbol: stock MDBT50Q-U1MV2 p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
Module VDD/VDDH decoupling
At pads 28/30, < 2 mm (Raytac ref. circuit 8.3: 10 uF)
USB VBUS (module pad 32) and second-stage USB ESD
R12 in series (nRF52840 PS 7.3 config 1): a legacy-cable hot plug rings the link VBUS to 6.5-8.4 V, above the 5.8 V VBUS abs max; with 4.7 R (Nordic's value) R12 x C12 filters the ring and the pin sees the settled VBUS, 4.49-5.49 V for a 4.5-5.5 V source (hardware/sim test_hotplug_nrf_vbus_abs_max)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
32.768 kHz LFXO
SC-20S CL 9 pF; Ccap = 2*CL - Cpin - Cpcb ~ 12 pF C0G. R1 <= 90k (nRF RS_LFXO max 100k); DLmax 0.5 uW = nRF PD_LFXO. At pads 17/18, traces < 5 mm, symmetric, GND guard; no copper under Y1.
QSPI NOR flash (128 Mbit)
nRF52840-DK QSPI pins (pads 41-46); traces < 20 mm, matched within 2 mm. -IQ suffix: QE=1 fixed, /WP and /HOLD disabled, so IO2/IO3 need no pull-ups. CS pulled up so the flash stays deselected in reset. Use deep power-down when idle.
SWD debug (Tag-Connect TC2030-NL)
Footprint only (no BOM part), TOP side under the OLED glass (SPEC section 8). Keep the 3 NPTH holes + cable-head area clear. No series parts on SWD. NRESET: internal pull-up, R11 is a DNP option.
NFC tag antenna (nRF52840 NFCT, NFC-A Type 2/4)
Coil between NFC1 and NFC2: its flex tail solders to pads J11 (coil in the top cover). Tune: Ctune = 2/((2*pi*13.56 MHz)^2 * L_coil) - Cp - Cint (Cint ~ 4 pF, PS 6.13); 180 pF C0G each suits L ~ 1.4-1.5 uH; retune on prototype. Route NFC1/NFC2 as a pair, away from the TMAG and the LED data line.
Spare GPIO test pads
Value = module GPIO (P0.03/P0.04 = AIN1/AIN2)
